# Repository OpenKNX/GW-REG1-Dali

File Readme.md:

# Infrared-Gateway
Can be used to receive and send ir-codes.

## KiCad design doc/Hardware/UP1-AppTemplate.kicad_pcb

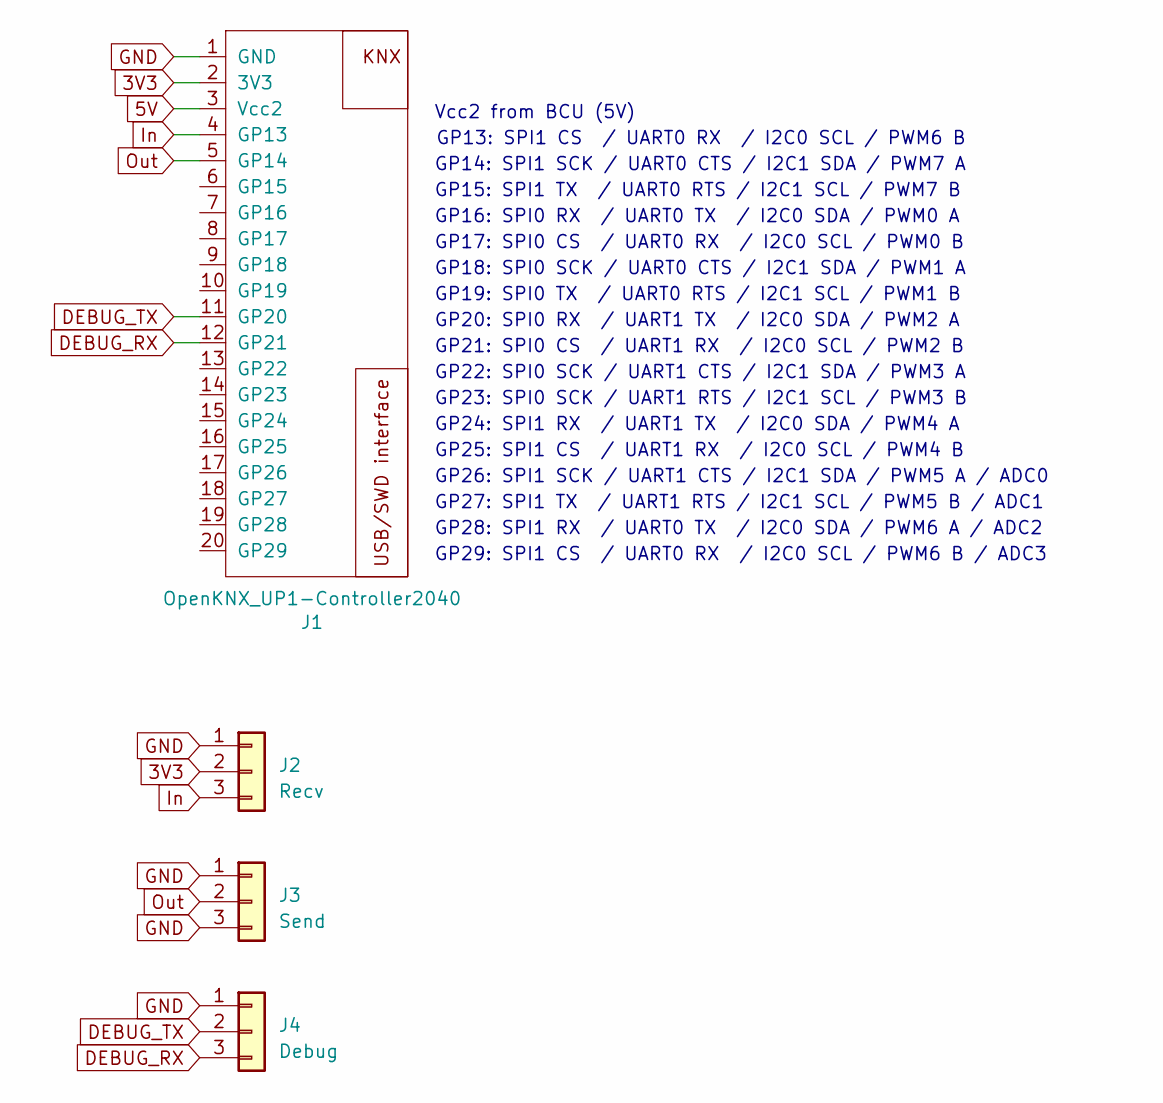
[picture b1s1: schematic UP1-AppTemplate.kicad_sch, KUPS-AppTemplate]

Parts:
J1: OpenKNX_UP1-Controller2040; OpenKNX_UP1-PCBConnector_1x20_App_3D; LCSC C2334
J2: Recv; PinHeader_1x03_P2.54mm_Vertical
J3: Send; PinHeader_1x03_P2.54mm_Vertical
J4: Debug; PinHeader_1x03_P2.54mm_Vertical

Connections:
3V3: J1.2 (3V3), J2.2
5V: J1.3 (Vcc2)
DEBUG_RX: J1.12 (GP21), J4.3
DEBUG_TX: J1.11 (GP20), J4.2
GND: J1.1 (GND), J2.1, J3.1, J3.3, J4.1
In: J1.4 (GP13), J2.3
Out: J1.5 (GP14), J3.2

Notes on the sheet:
GP16: SPI0 RX / UART0 TX / I2C0 SDA / PWM0 A
GP26: SPI1 SCK / UART1 CTS / I2C1 SDA / PWM5 A / ADC0
GP20: SPI0 RX / UART1 TX / I2C0 SDA / PWM2 A
Vcc2 from BCU (5V)
GP15: SPI1 TX / UART0 RTS / I2C1 SCL / PWM7 B
GP22: SPI0 SCK / UART1 CTS / I2C1 SDA / PWM3 A
GP13: SPI1 CS / UART0 RX / I2C0 SCL / PWM6 B
GP25: SPI1 CS / UART1 RX / I2C0 SCL / PWM4 B
GP21: SPI0 CS / UART1 RX / I2C0 SCL / PWM2 B
GP14: SPI1 SCK / UART0 CTS / I2C1 SDA / PWM7 A
GP19: SPI0 TX / UART0 RTS / I2C1 SCL / PWM1 B
GP17: SPI0 CS / UART0 RX / I2C0 SCL / PWM0 B
GP28: SPI1 RX / UART0 TX / I2C0 SDA / PWM6 A / ADC2
GP27: SPI1 TX / UART1 RTS / I2C1 SCL / PWM5 B / ADC1
GP18: SPI0 SCK / UART0 CTS / I2C1 SDA / PWM1 A
GP23: SPI0 SCK / UART1 RTS / I2C1 SCL / PWM3 B
GP24: SPI1 RX / UART1 TX / I2C0 SDA / PWM4 A
GP29: SPI1 CS / UART0 RX / I2C0 SCL / PWM6 B / ADC3

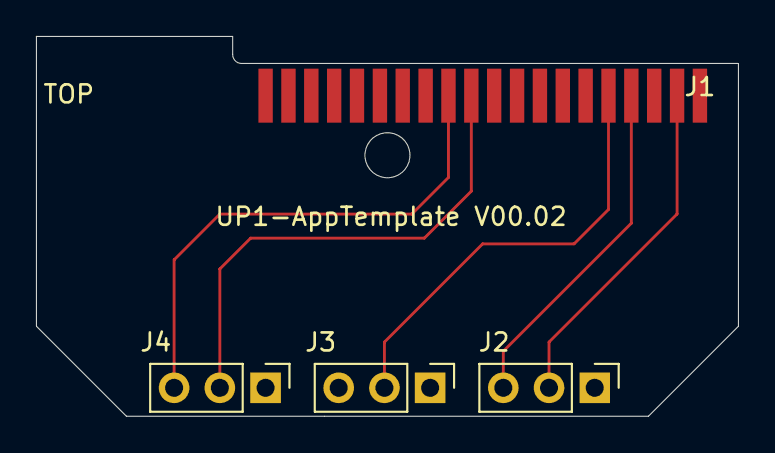
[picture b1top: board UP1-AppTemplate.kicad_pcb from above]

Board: 2 copper layers, 39.0 x 21.1 mm, 4 parts (0 on the bottom side), 6 nets.

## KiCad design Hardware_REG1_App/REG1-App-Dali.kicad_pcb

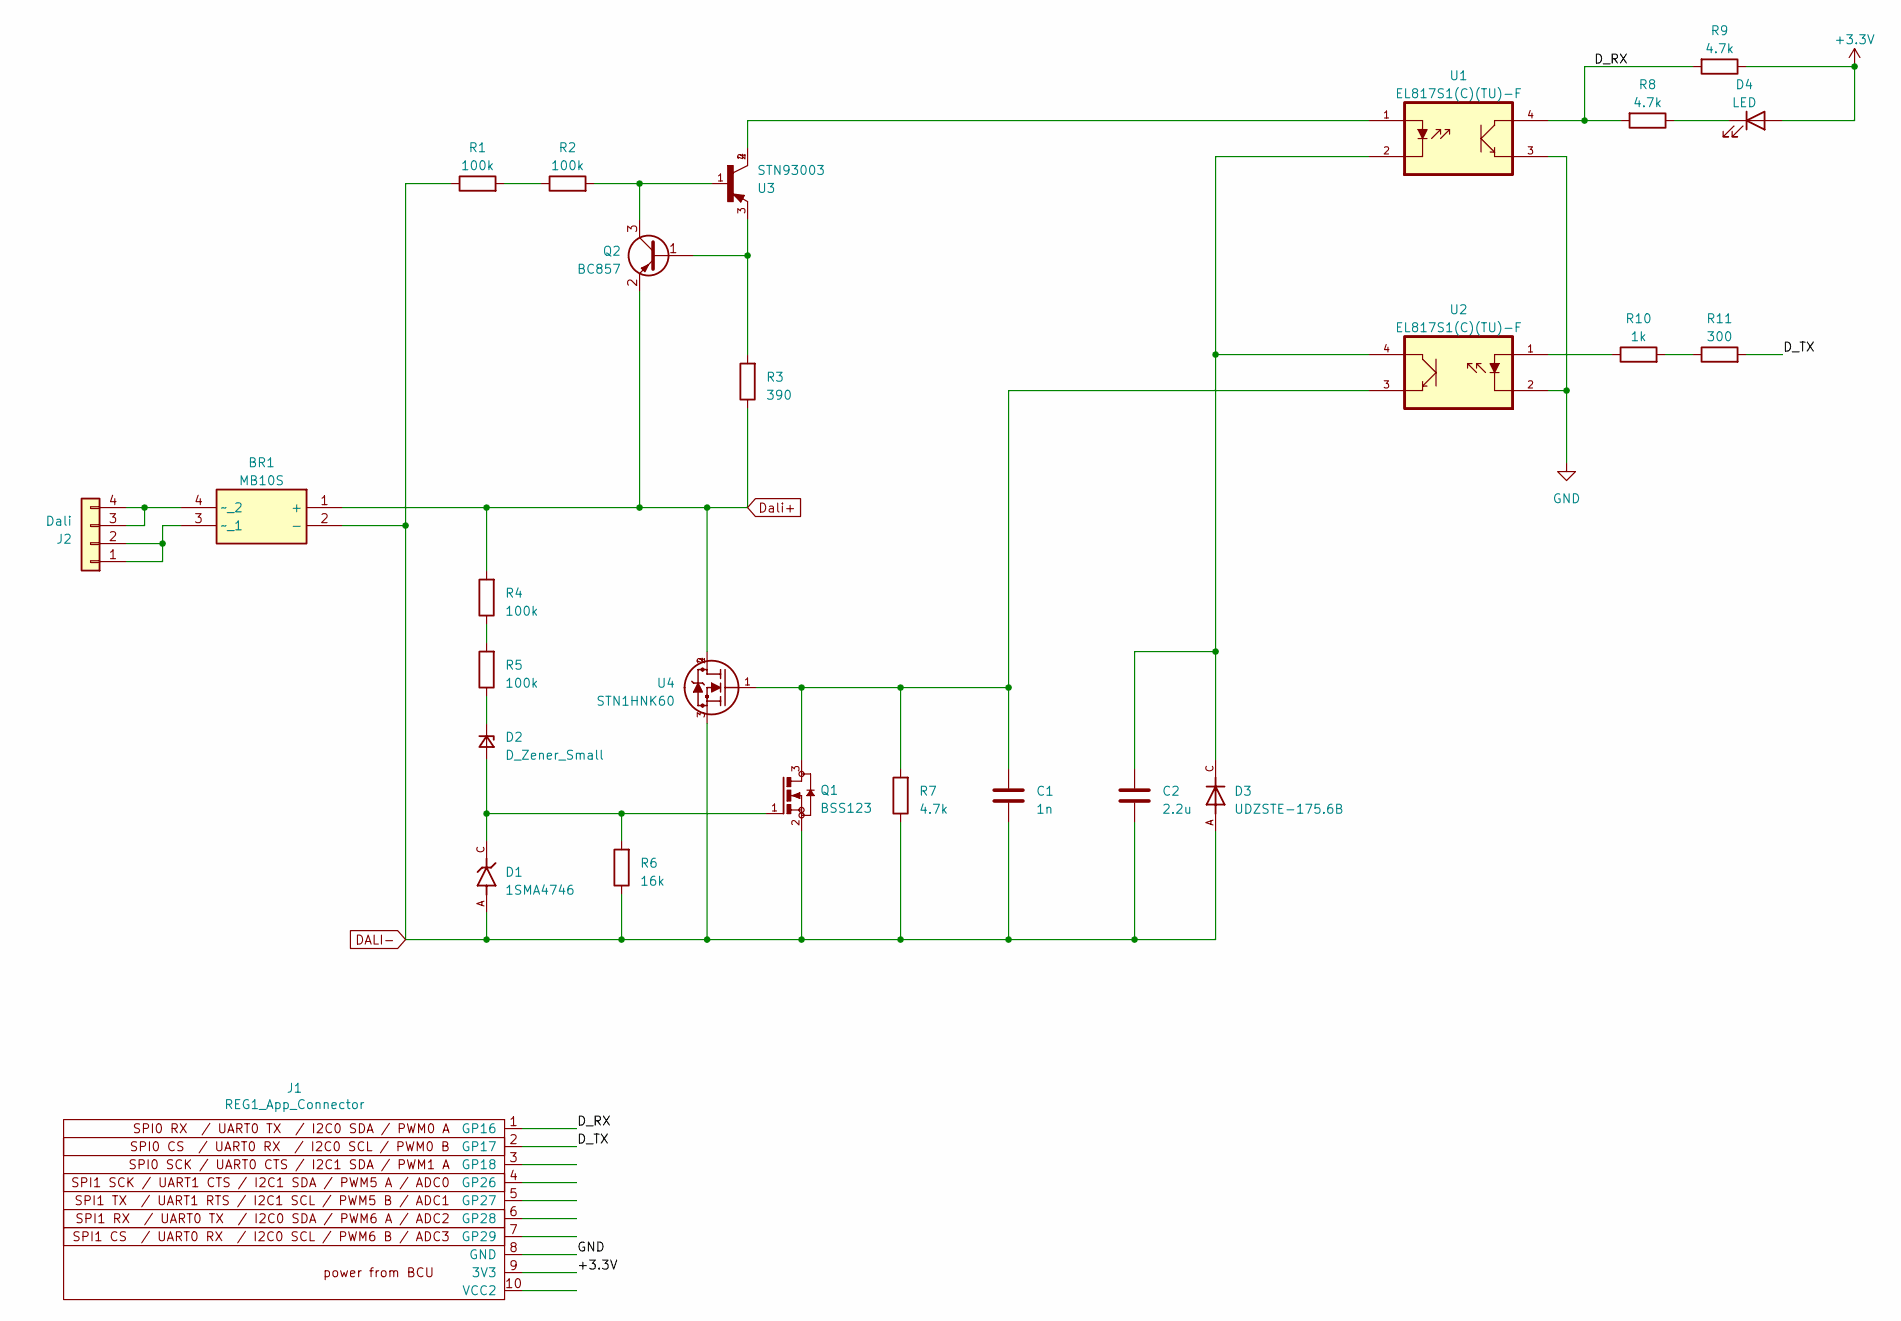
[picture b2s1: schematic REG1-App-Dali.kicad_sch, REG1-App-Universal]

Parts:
BR1: MB10S; SOP245P670X290-4N; Manufacturer_Part_Number MB10S; Mouser Part Number 512-MB10S
C1: 1n; C_0603_1608Metric
C2: 2.2u; C_0805_2012Metric
D1: 1SMA4746; DIOM4325X250N; PARTREV B2102
D2: D_Zener_Small; D_SOD-123
D3: UDZSTE-175.6B; SODFL2512X90N
D4: LED; LED_0603_1608Metric
J1: REG1_App_Connector; PinHeader_1x10_P2.54mm_Horizontal
J2: Dali; PhoenixContact_MC_1,5_4-G-3.5_1x04_P3.50mm_Horizontal
Q1: BSS123; SOT23
Q2: BC857; SOT-23
R1, R2, R4, R5: 100k; R_1206_3216Metric
R3: 390; R_0603_1608Metric
R6: 16k; R_0805_2012Metric
R7, R8, R9: 4.7k; R_0603_1608Metric
R10: 1k; R_1206_3216Metric
R11: 300; R_1206_3216Metric
U1, U2: EL817S1(C)(TU)-F; SOIC254P1030X390-4N
U3: STN93003; SOT230P700X180-4N
U4: STN1HNK60; SOT-223; MANUFACTURER_PART_NUMBER STN1HNK60

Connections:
+3.3V: D4.2 (A), J1.9 (3V3), R9.1
/D_RX: J1.1 (GP16), R8.2, R9.2, U1.4
/D_TX: J1.2 (GP17), R11.2
DALI-: BR1.2 (-), C1.2, C2.2, D1.A, D3.A, Q1.2, R1.1, R6.1, R7.1, U4.3
Dali+: BR1.1 (+), Q2.2 (E), R3.1, R4.2, U4.2, U4.4
GND: J1.8 (GND), U1.3, U2.2
unnamed: BR1.3 (~_1), J2.1, J2.2
unnamed: BR1.4 (~_2), J2.3, J2.4
unnamed: C1.1, Q1.3, R7.2, U2.3, U4.1
unnamed: C2.1, D3.C, U1.2, U2.4
unnamed: D1.C, D2.2 (A), Q1.1, R6.2
unnamed: D2.1 (K), R5.1
unnamed: D4.1 (K), R8.1
unnamed: Q2.1 (B), R3.2, U3.3
unnamed: Q2.3 (C), R2.2, U3.1
unnamed: R1.2, R2.1
unnamed: R4.1, R5.2
unnamed: R10.1, U2.1
unnamed: R10.2, R11.1
unnamed: U1.1, U3.2, U3.4

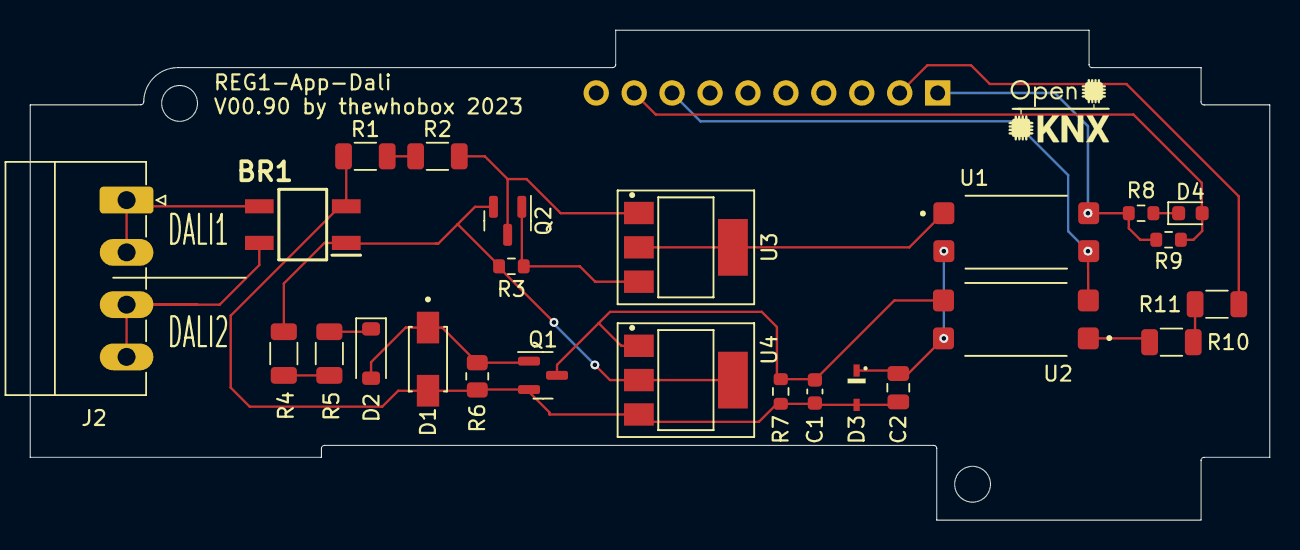
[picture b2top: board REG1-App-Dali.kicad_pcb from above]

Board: 2 copper layers, 83.0 x 32.8 mm, 26 parts (1 on the bottom side), 20 nets.

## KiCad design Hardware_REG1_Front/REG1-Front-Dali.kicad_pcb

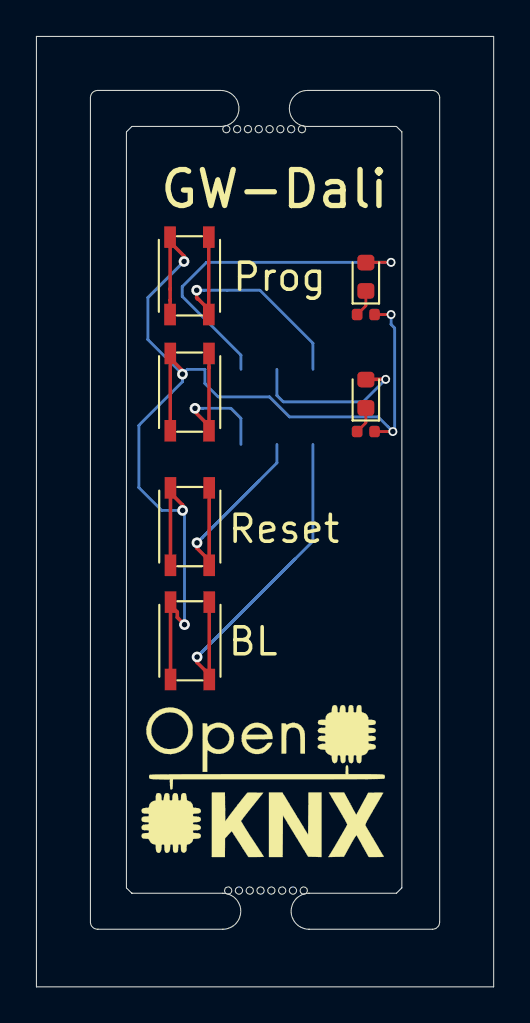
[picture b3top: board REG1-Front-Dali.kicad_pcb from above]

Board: 2 copper layers, 25.4 x 52.8 mm, 11 parts (1 on the bottom side), 9 nets.

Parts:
D1: Prog; LED_0603_1608Metric
D2: Func; LED_0603_1608Metric
J1: Conn_02x04_Odd_Even; PinHeader_2x04_P2.00mm_Vertical_SMD
R1, R2: R; R_0402_1005Metric
SW1: Prog; SW_Push_Xunpu_TS-1089S
SW2: Func; SW_Push_Xunpu_TS-1089S
SW3: Res; SW_Push_Xunpu_TS-1089S
SW4: BL; SW_Push_Xunpu_TS-1089S
mouse-bite: VAL**; mouse-bite-5.00mm-frame
mouse-bite#2: VAL**; mouse-bite-5.00mm-frame

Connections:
BOOTSEL_F: J1.8, SW4.1
GND: J1.1, R1.1, R2.1, SW1.2, SW2.2, SW3.2, SW4.2
GPIO03: D2.2, J1.5
GPIO24: J1.4, SW2.1
unnamed: D1.1, R1.2
unnamed: D2.1, R2.2
PROGBTN: J1.7, SW1.1
PROGLED: D1.2, J1.3
RUN: J1.6, SW3.1

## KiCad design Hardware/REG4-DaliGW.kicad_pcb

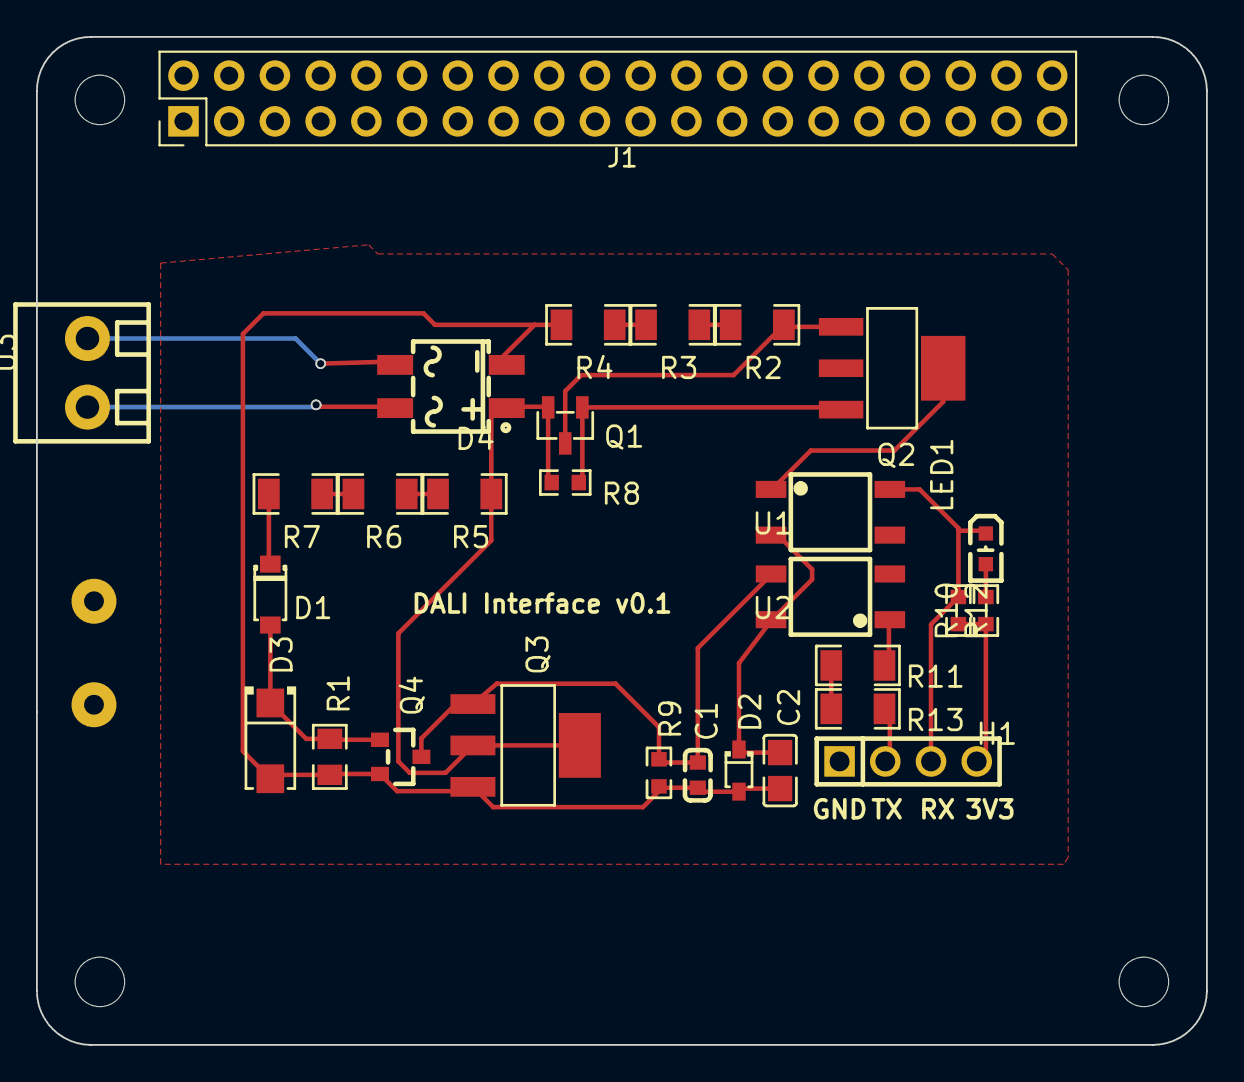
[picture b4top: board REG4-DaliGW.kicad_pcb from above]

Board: 2 copper layers, 65.0 x 56.0 mm, 30 parts (1 on the bottom side), 22 nets.

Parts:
C1: 1nF; C0603
C2: 2.2uF; C0805
D1: MMSZ4711T1G; SOD-123_L2.8-W1.8-LS3.7-RD
D2: UDZSTE-175.6B; SOD-323_L1.8-W1.3-LS2.5-RD
D3: 1SMA4746; SMA_L4.4-W2.5-LS5.2-R-RD
D4: MB10S_C2488; MBS_L4.7-W3.8-P2.40-LS7.0-TL
H1: 210-91-04GB01; HDR-TH_4P-P2.54-V-M
J1: Conn_02x20_Odd_Even; PinHeader_2x20_P2.54mm_Vertical
J2: Conn_KNX; KNX_Connector
LED1: 0603White light_C2290; LED0603-R-RD_WHITE
Q1: BC857C,215; SOT-23-3_L2.9-W1.3-P1.90-LS2.4-BR
Q2: STN93003; SOT-223-4_L6.5-W3.5-P2.30-LS7.0-BR
Q3: STN1HNK60; SOT-223-3_L6.5-W3.4-P2.30-LS7.0-BR
Q4: BSS123; SOT-23_L2.9-W1.3-P1.90-LS2.4-BR
R1: 16kΩ; R0805
R2, R3, R4, R5, R6, R7: 68kΩ; R1206
R8: 390Ω; R0603
R9, R10, R12: 4.7kΩ; R0603
R11: 1kΩ; R1206
R13: 300Ω; R1206
U1, U2: EL357N(C)(TA)-G; OPTO-SMD-4_L4.4-W4.1-P2.54-LS7.0-TL
U3: DB125-3.81-2P; CONN-TH_2P-P3.81_L7.4-W7.6

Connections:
3V3: H1.4, R10.2, R12.2
D2_1: C2.2, D2.1, U1.2, U2.4
DALI+: D4.1, Q1.2, Q3.2, Q3.4, R5.1, R8.1
DALI-: C1.1, C2.1, D2.2, D3.1, D4.2, Q3.3, Q4.2, R1.1, R4.1, R9.1
D_RX: H1.3, LED1.2, R10.1, U1.4
D_TX: H1.2, R13.2
GND: H1.1, U1.3, U2.2
LED1_1: LED1.1, R12.1
Q1_1: Q1.1, Q2.3, R8.2
Q1_3: Q1.3, Q2.1, R2.2
Q2_4: Q2.4, U1.1
Q3_1: C1.2, Q3.1, Q4.3, R9.2, U2.3
Q4_1: D1.2, D3.2, Q4.1, R1.2
R3_2: R2.1, R3.2
R4_2: R3.1, R4.2
R5_2: R5.2, R6.2
R6_1: R6.1, R7.1
R7_2: D1.1, R7.2
R11_2: R11.2, R13.1
U2_1: R11.1, U2.1
U3_1: D4.4, U3.1
U3_2: D4.3, U3.2

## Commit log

2023-05-12 init
2023-05-13 added new interface
2023-05-27 added pio project
2023-05-27 small changes
2023-05-28 added dali response
2023-05-28 chaned debug port
2023-05-30 updated gitignore
2023-05-31 added REG1
2023-06-01 added ae-manu
2023-06-06 added DALI lib
2023-06-07 added urls
2023-06-07 updated ae-manu
2023-06-11 added channels
2023-06-11 added switching
2023-06-13 added functionProperties
2023-06-13 renamed queue
2023-06-14 added lock
2023-06-14 small fixes
2023-06-18 added DaliBusState
2023-06-19 added group channels
2023-06-20 updated platform
2023-06-20 fixed group min
2023-06-20 added groups and minimized in one channel
2023-06-21 added scan
2023-06-22 Added assign Address
2023-06-22 removed launch.json
2023-06-22 removed tasks.json
2023-06-25 changed send behave
2023-06-26 small addressing changes
2023-06-26 send changes
2023-06-27 updated pcb
2023-06-28 updated REG1 and renamed
2023-07-02 fix addressing
2023-07-04 added day/night
2023-07-05 added setOnValue CO
2023-07-07 fixed bugs in knxprod
2023-07-10 updated front
2023-07-10 upgraded messagequeue thread safe
2023-07-10 removed C#
2023-07-11 added scenes
2023-07-12 fixed missing nullptr
2023-07-13 replaced broadcast
2023-07-13 added auto addressing
2023-07-17 Added usb hid responses
2023-07-19 fix usb
2023-07-20 update for setup1
2023-07-20 moved include
2023-07-21 moved dependences to library.json
2023-07-23 removed library json
2023-07-28 enhancements for ini
2023-07-28 fixed setup
2023-08-01 added relative dimm
2023-08-02 added QueryError and BusState
2023-08-03 relative dimm enhancement
2023-08-15 fixed relative dimm
2023-08-29 Updated to FileTransferModule
2023-08-31 removed updater
2023-10-01 added rgb
2023-10-09 added XY, small fixes bri status
2023-10-16 added group states to evg
2023-10-16 changed log info to debug
2023-10-18 updated ini
2023-10-18 colorhelper add kelvin
2023-10-18 changed dali commands
2023-10-19 updated knxprod rgb single dimm
2023-10-22 fixes stack overflow, added group state to single
2023-10-29 added rtt
2023-10-30 added extern
2023-10-30 changed main for extern
2023-10-30 updated knxprod
2023-10-30 changed addModules to reference
2023-11-05 changed Hardware Serial
2023-11-07 adapted to REG1-V1 and JLCPCB fabrication toolkit
2023-11-08 changed knxprod naming and pio envs
2023-11-10 fixed user content werte
2023-11-10 fixed missing memory
2023-11-10 added scripts
2023-11-12 fixed script
2023-11-14 updated script
2023-11-20 prepared for etsfix
2023-11-23 added evg read/write
2023-11-23 small fix
2023-11-25 fixed evg read
2023-12-03 added tunable white
2023-12-05 REG1-App-Dali V00.90
2023-12-05 moved hardware into OpenKNX repo structure
2023-12-12 small enhancements
2023-12-13 scan test
2023-12-15 init test2
2023-12-15 added serial
2023-12-15 debug fix
2023-12-16 added processCommand
2023-12-17 commands renamed
2023-12-18 added showHelp
2024-01-02 Added delay for scanning
2024-01-03 added new-clone script
2024-01-03 fixed path
2024-01-05 fixed typo updated knxprod
2024-01-06 updated todo
2024-01-07 added activity and v1
2024-01-11 updated project structure
2024-01-11 updated upload script
2024-01-11 updated scripts
2024-01-11 fixed script path
2024-01-11 fixed checkout
2024-01-11 fixed
2024-01-11 fixed restore
2024-01-11 added task
2024-01-11 changed lang
2024-01-12 changed functionProperty IDs
2024-01-13 some fixes of todo
2024-01-14 added item to todo
2024-01-15 added abs+rel dim for r g b
2024-01-16 fixed color abs
2024-01-17 fixed reference
2024-01-17 added errorLED
2024-01-17 fix error led on v0
2024-01-22 added badge
2024-01-22 small codefactor
2024-01-22 fix error
2024-01-24 added pt-enums and interv for ko change
2024-01-25 moved hardware
2024-01-25 led fixes
2024-01-26 moved firmware in root
2024-01-26 removed pointer
2024-01-26 added point to todo
2024-01-27 updated dependencies
2024-01-30 script changes
2024-01-31 common test
2024-02-02 wip: evg query level
2024-02-02 feature: func button
2024-02-02 fix: func button handler
2024-02-02 fix: daliActivity
2024-02-02 refact: func button
2024-02-03 fix: query level
2024-02-03 updated version
2024-02-04 added debug output
2024-02-05 wip: rel. dimm
2024-02-07 added: color xyY
2024-02-07 feature: increased scene mapping to 64
2024-02-07 fix: scene allocator
2024-02-13 code refactor
2024-02-13 fix: dependencies.txt updated
2024-02-13 fix: relative dimm
2024-02-20 added: xyY ignore Y
2024-02-23 wip: esp32 support
2024-02-24 wip: save color to scene
2024-02-26 wip: color to scene
2024-02-26 wip: scene to color
2024-02-27 fix: dualcore
2024-02-28 fix typo and updated dependencies
2024-03-01 added: set dimmstate interval
2024-03-02 updated dependencies and fixed restore script
2024-03-04 wip: luba
2024-03-07 added: setting for dimmduration and identify
2024-03-07 fix: save level to scene
2024-03-09 wip: fix scenes
2024-03-10 fix: read scene color temp
2024-03-12 wip: hcl
2024-03-19 added: hcl sun offset
2024-03-25 wip: hcl added actions auto-manu
2024-03-26 wip: moved timer to module
2024-03-26 fix: dependencies.txt
2024-04-08 fix: build+upload script
2024-04-11 fix: DT50-52 in ETS
2024-04-11 change: adde ShowInComObjectTree
2024-04-15 changed: updated dali commands
2024-04-16 changed new addrloop
2024-04-16 wip: enhanced scan
2024-04-29 minimize to finde tl bug
2024-04-30 fix: knxprod header & activated dma
2024-05-06 fix: messagequeue memoryleak
2024-05-16 fix: unconfigured scan
2024-05-26 update knxprod
2024-06-02 wip: dali settings as float
2024-06-05 wip: percent as floats
2024-06-06 wip: script changes for float parameters
2024-06-09 wip: hcl in groups
2024-06-10 wip: hcl bri and kos for scene/curve
2025-02-05 added: mutex
2025-02-07 added: help for step commands
2025-02-07 added: help for getlvl command
2025-02-07 added: invalid addr check
2025-02-07 fix: pinmode
2025-02-07 moved pinmode up
2025-02-07 fix: queue handling mutex
2025-02-10 fix: remove idleCount from Search
2025-02-10 fix: missing }
2025-02-10 added: printfs
2025-02-10 added: printf
2025-02-10 fix: query short
2025-02-12 test delay
2025-02-13 changed: Queue push
2025-02-13 removed: delay when compare
2025-02-13 fix: verify short address
2025-02-13 fix: build errors
2025-02-13 fix: log error now as info for new address
2025-02-13 fix: output of getLvl
2025-02-23 fix: MessageQueue mutex
2025-03-01 fix: broadcast crash
2025-03-01 fix: broadcast crash on other kos
2025-03-04 update to new lib
2025-03-05 building esp
2025-03-05 removed v0 environemnts
2025-03-06 removed: core1
2025-03-06 fix: added process daliMaster
2025-03-08 fix: call dali process
2025-03-10 removed: manually sending configuration commands twice
2025-03-10 fix: ets evg read scripts
2025-03-10 fix: script assign short address with long address
2025-03-10 fix: save kelvin to scene
2025-03-14 added: first ethernet
2025-03-14 fix: custom.ini for esp dev2
2025-03-16 added: iot-gateway
2025-03-18 added: iot-gw to workspace
2025-03-20 added: defines for webui
2025-03-21 added: webui module to openknx
2025-03-21 fix: DaliGateway only if arch is esp
2025-03-21 removed: dali gateway loop
2025-03-23 fix: Module return version
2025-03-24 added: script for processing web files
2025-03-24 fix: for renamed iotgateay
2025-03-26 fix: replace webui with network
2025-03-27 added: wiki link for webserver
2025-03-27 fix: webserver link moved
2025-04-12 added: esp release test
2025-04-12 feat: add english translations
2025-04-14 use: new hardware definition
2025-04-14 fix: addresses
2025-04-15 fix: dimmLock
2025-04-17 imported translations from pr#3
2025-04-24 fix: type; added: KO-Offset to base define
2025-05-09 fix: update sendExtendedCommand to include _isGroup parameter
2025-05-24 fix: relative dimming
2025-06-09 changed relative dimming
2025-06-12 fix: turn on/off with relative dimming
2025-06-15 changed: firmware names
2025-07-09 fix: turn on brightness on hcl
2025-07-11 fix: compile warning
2025-07-19 fix: hcl turn on brightness
2025-08-16 fix: relative dimming status with groups
2025-08-16 add: status for colour xy
2025-08-16 bump version
2025-08-16 fix: knxprod
2025-08-18 fix: ignore temp or bri if its not activated in hcl curve
2026-02-11 fix build errors
2026-02-14 prepare 0.9.6 with REG1-LAN-TP-Dali
2026-02-14 updated: dependencies
2026-02-17 init umbau
2026-02-18 tests with moduledefs
2026-02-20 moved OFM-Dali to own repo
2026-02-20 removed orga
2026-02-20 added groups
2026-02-20 removed old ofm
2026-02-20 wip: added scenes
2026-02-21 added: hcl
2026-02-27 changed: ModuleType usings
2026-03-07 fix: build scripts
2026-03-12 fix on/off with relativ dimm setting blocking dimm fucntion
    The removed code blocked the whole dimming function when the 'block turn on
    with relitv dimm' setting was active. It is just removed because it was
    redundant with a working version of it in DaliChannel::loopDimming().
2026-03-12 fix brigthness value at end of dimming
    change the dimmstatus request to be send after the UP / DOWN dali
    commands and send an additional request on the end of dimming to keep
    the status in sync with the EVG.
2026-03-12 fix switch status on relativ dimm
    do not call updateCurrentDimmValue() on end of dimming. The update of
    the dimming vlaue is handeled by sending the additional Dali Query.
    The reason for removing it is, the function did send some wrong switch status to KNX when a minimum
    dimming level othe than 0 is applied to the EVG.
2026-03-12 do not start relativ dimm down when device state is off
2026-03-25 fix: build rp2040
2026-03-31 move dalimodule to second core or seperate thread to fix scan issue
2026-05-07 Umbau (#17)
    * init umbau
    * tests with moduledefs
    * wip
    * wip
    * moved OFM-Dali to own repo
    * removed orga
2026-05-11 fix race condition in setup logik of dali and knx module
2026-05-13 fix #18
2026-05-13 fix firmware names so release zip is generated correctly.
2026-05-13 fix: bump knxprod version
2026-05-14 fix: dali-iot-gateway with webserver
2026-05-16 fix(esp32): pin daliMaster loop task to core 1 with elevated priority
    The ESP32 DALI loop task was created with xTaskCreateUniversal at
    priority 0 (idle) and pinned to core 0 (PRO_CPU). Core 0 hosts WiFi,
    lwIP and Ethernet tasks, so the DALI master process was competing
    directly with KNX/IP traffic. Combined with idle priority, the task
    was preempted whenever the gateway saw KNX activity.
    Move the task to APP_CPU (core 1) at priority 5, isolated from the
2026-05-16 fix(esp32): pin daliMaster loop task to core 1 with elevated priority (#20)
    The ESP32 DALI loop task was created with xTaskCreateUniversal at
    priority 0 (idle) and pinned to core 0 (PRO_CPU). Core 0 hosts WiFi,
    lwIP and Ethernet tasks, so the DALI master process was competing
    directly with KNX/IP traffic. Combined with idle priority, the task
    was preempted whenever the gateway saw KNX activity.
    Move the task to APP_CPU (core 1) at priority 5, isolated from the
2026-05-20 fix: iot init
2026-05-26 migrate: to new openknx webserver
2026-06-17 fix: iotgateway initialisation; update

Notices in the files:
Hardware_REG1_Front/REG1-Front-Dali.kicad_pcb:
V00.01 © thewhobox, 2023
